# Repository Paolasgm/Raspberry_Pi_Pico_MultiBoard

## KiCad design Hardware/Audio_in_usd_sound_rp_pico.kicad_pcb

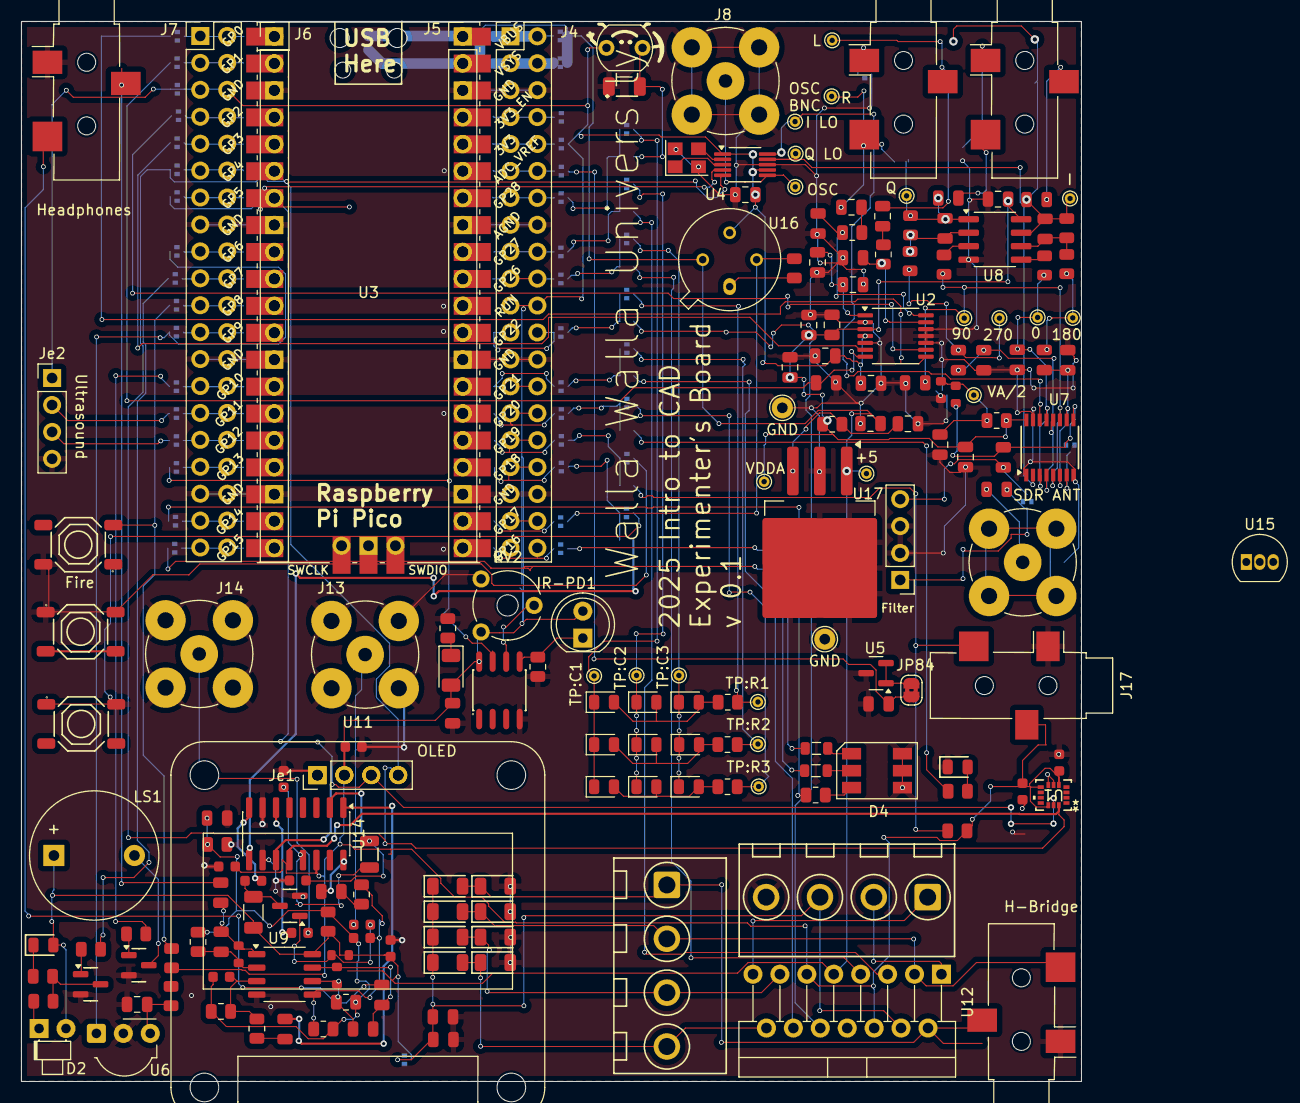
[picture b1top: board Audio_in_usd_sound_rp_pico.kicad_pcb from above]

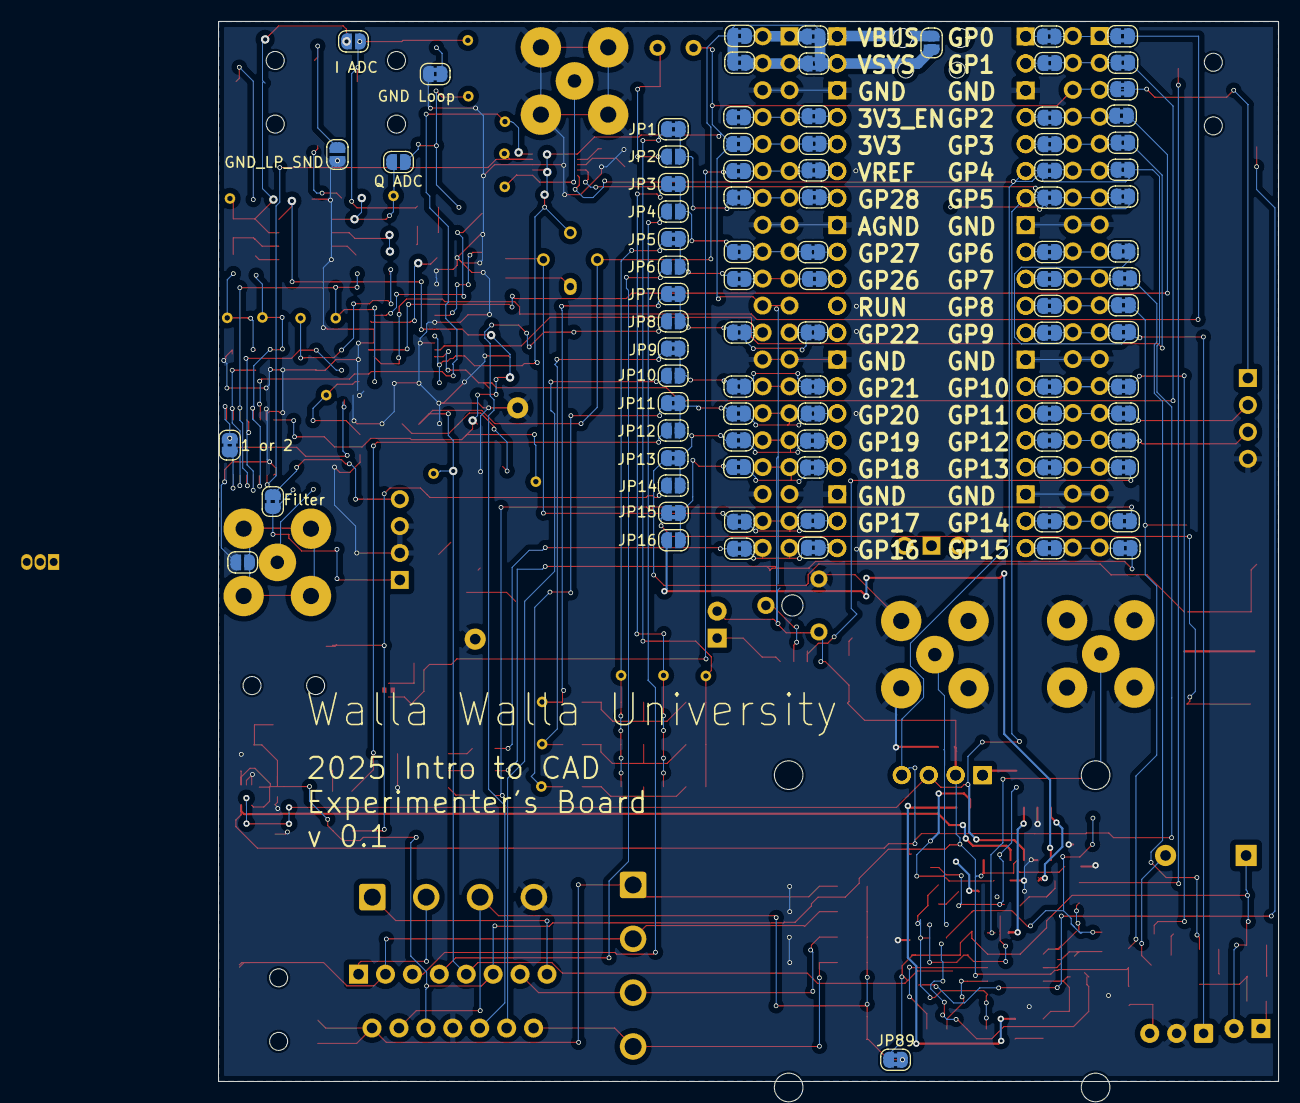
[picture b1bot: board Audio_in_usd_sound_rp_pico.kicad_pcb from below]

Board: 4 copper layers, 100.0 x 100.0 mm, 275 parts (88 on the bottom side), 189 nets.

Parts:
C2, C38, C41, C47, C48, C52: 100nF; C_0603
C3, C4: 1uF; C_0805_2012Metric
C6, C7, C16, C21, C22, C24, C27: 4.7nF; C_0805
C8, C9, C12, C56, C57: 10uF; C_0805_2012Metric
C10, C13, C17: 0.1uF; C_0805_2012Metric
C11, C15, C20, C23, C30, C55: 0.1u; C_0805_2012Metric
C14, C33, C42: 220pF; C_0805
C18, C19, C25, C26, C46: 1uF; C_0805
C28, C29: 100pF; C_0805
C31, C32, C39, C40, C44, C45: 10uF; C_0805
C34, C43: 10nF; C_0603
C35, C54: 2.2nF; C_0603
C36, C37: 22pF; C_0603
C49, C50, C51: 100nF; C_0805
D1, D3: Green; D_0805
D2: IR LED IR908-7C-F; LED_D1.8mm_W1.8mm_H2.4mm_Horizontal_O1.27mm_Z8.2mm
D4: C784540; LED footprint
D5, D6, D7, D8, D9, D10, D11, D12: 1N4004W; D_SOD-123FL
D13, D14, D15, D16, D17, D18, D19, D20, D21: LED; LED_0805_2012Metric
IR-LED1: IR26-21C_L110_TR8; LED_1206_3216Metric
IR-PD1: D_Photo; LED_D5.0mm
J1: ADC IN; Jack_3.5mm_CUI_SJ-3523-SMT_Horizontal
J4: Conn_02x20_Counter_Clockwise; PinSocket_2x20_P2.54mm_Vertical_Counterclockwise
J5, J6: Conn_01x20; PinHeader_1x20_P2.54mm_Vertical
J7: Conn_02x20_Counter_Clockwise; PinSocket_2x20_P2.54mm_Vertical
J8: BNC; BNC_TEConnectivity_1478204_Vertical
J11: SDR ANT; BNC_TEConnectivity_1478204_Vertical
J12: SDR Out; Jack_3.5mm_CUI_SJ-3523-SMT_Horizontal
J13, J14: ANT_BNC; BNC_TEConnectivity_1478204_Vertical
J15, J16: Audio IN; Jack_3.5mm_CUI_SJ-3523-SMT_Horizontal
J17: Mini-jack socket; Jack_3.5mm_CUI_SJ-3523-SMT_Horizontal
JP1, JP3, JP5, JP7, JP9, JP11, JP13, JP15, JP17, JP20, JP21, JP22, JP23, JP24, JP25, JP26, JP27, JP28, JP29, JP30, JP31, JP32, JP33, JP34, JP35, JP36, JP37, JP38, JP39, JP40, JP41, JP42, JP43, JP44, JP45, JP46, JP47, JP48, JP49, JP51, JP52, JP53, JP54, JP55, JP56, JP57, JP58, JP59, JP60, JP61, JP62, JP63, JP64, JP65, JP66, JP67, JP68, JP69, JP70, JP71, JP72, JP73, JP74, JP75, JP76, JP77, JP78, JP79, JP80, JP81, JP82, JP83, JP84, JP86, JP87, JP89: Jumper_2_Bridged; SolderJumper-2_P1.3mm_Bridged2Bar_RoundedPad1.0x1.5mm
JP2, JP4, JP6, JP8, JP10, JP12, JP14, JP16: Jumper_2_Open; SolderJumper-2_P1.3mm_Open_RoundedPad1.0x1.5mm
JP18, JP19, JP88: GND_LP_SND; SolderJumper-2_P1.3mm_Open_RoundedPad1.0x1.5mm
JP50: USB Only; SolderJumper-2_P1.3mm_Open_RoundedPad1.0x1.5mm
JP85: Groundloop RX_NS; SolderJumper-2_P1.3mm_Open_RoundedPad1.0x1.5mm
Je1, Je2: Conn_01x04_Socket; PinHeader_1x04_P2.54mm_Vertical_Female
Je3: Filter; PinHeader_1x04_P2.54mm_Vertical_Female
LS1: Speaker; Buzzer_12x9.5RM7.6
Q1, Q2: MMBT2222A 1P; Q_SOT-23
Q3: MMBT2222A; Q_SOT-23
R1: 10kΩ; R_0603
R2, R3: 200; R_0805_2012Metric
R4, R31, R43: 100Ω; R_0805
R5: 68Ω; R_0805
R6, R42: 10kΩ; R_0805
R7, R8: 1kΩ; R_0805
R9: 33Ω; R_0805
R10, R20: 39kΩ; R_0603
R11: 1kΩ; R_0603
R12: 10k; R_0805_2012Metric
R13, R14, R15, R16: 10Ω; R_0805
R17, R18, R29, R30: 2kΩ; R_0805
R19, R25: 15k; R_0805_2012Metric
R21, R27: 8.2k; R_0805_2012Metric
R22: 100kΩ; R_0603
R23, R28: 3.9k; R_0805_2012Metric
R24: 1k; R_1206_3216Metric
R32: B 100Ω; L_0805_2012Metric
R33: G 100Ω; L_0805_2012Metric
R34: R 300Ω; R_0805_2012Metric
R35: 10K; R_0805_2012Metric
R36: 270R; R_0805_2012Metric
R37: PhotoResistor; R_LDR_5.1x4.3mm_P3.4mm_Vertical
R38: 1kΩ; R_1206_3216Metric
R39, R40, R41: 680; R_0805_2012Metric
R44: 1; R_0805_2012Metric
RV2: R_Potentiometer_US; Potentiometer_Piher_PT-6-V_Vertical_Hole
S2: Tactile Button, 160gf; SW-SMD_4P-L5.1-W5.1-P3.70-LS6.5-TL-2
SW1: Left; SW-SMD_4P-L5.1-W5.1-P3.70-LS6.5-TL-2
SW2: Right; SW-SMD_4P-L5.1-W5.1-P3.70-LS6.5-TL-2
T1, T2: Screw Terminal, 4Px5.08mm, 20A; CONN-TH_4P-P5.08_DB129VG-5.08-4P-GN-S
TP1: L; TestPoint_THTPad_D1.0mm_Drill0.5mm
TP2: R; TestPoint_THTPad_D1.0mm_Drill0.5mm
TP3: I LO; TestPoint_THTPad_D1.0mm_Drill0.5mm
TP4: Q LO; TestPoint_THTPad_D1.0mm_Drill0.5mm
TP5: OSC; TestPoint_THTPad_D1.0mm_Drill0.5mm
TP10, TP12: GND; TestPoint_THTPad_D2.0mm_Drill1.0mm
TP11: VA/2; TestPoint_THTPad_D1.0mm_Drill0.5mm
TP13: 180; TestPoint_THTPad_D1.0mm_Drill0.5mm
TP14: 0; TestPoint_THTPad_D1.0mm_Drill0.5mm
TP15: 270; TestPoint_THTPad_D1.0mm_Drill0.5mm
TP16: 90; TestPoint_THTPad_D1.0mm_Drill0.5mm
TP17: I; TestPoint_THTPad_D1.0mm_Drill0.5mm
TP18: Q; TestPoint_THTPad_D1.0mm_Drill0.5mm
TP25: +5; TestPoint_THTPad_D1.0mm_Drill0.5mm
TP26: VDDA; TestPoint_THTPad_D1.0mm_Drill0.5mm
TP:C1, TP:C2, TP:C3: TestPoint; TestPoint_THTPad_D1.0mm_Drill0.5mm
TP:R1, TP:R2, TP:R3: TestPoint; TestPoint_THTPad_D1.0mm_Drill0.5mm
U1: LSM6DSO32TR; LGA-14L_2P5X3X0P83_STM
U2: PCM1808PWR; TSSOP-14_4.4x5mm_P0.65mm
U3: Pico; RPi_Pico_SMD_TH
U4: MS5351M; MSOP-10_3x3mm_P0.5mm
U5: CJ431; SOT-23
U6: TSOP4438; Vishay_MOLD-3Pin
U7: PI5C3253CQEX; SSOP-16_3.9x4.9mm_P0.635mm
U8: OPA1612AxD; SOIC-8_3.9x4.9mm_P1.27mm
U9: LM358; SOP-8_3.9x4.9mm_P1.27mm
U11: HS96L03W2C03; OLED
U12: L298N; TO-220-15_P2.54x2.54mm_StaggerOdd_Lead4.58mm_Vertical
U13: LM393DR2G; SOIC-8_L5.0-W4.0-P1.27-LS6.0-BL
U14: Si4732; SOIC-16_3.9x9.9mm_P1.27mm
U15: DS18B20A10T6; TO-92_Inline
U16: TO-33-4_Window-Taylan
U17: LM2937xS; TO-263-3_TabPin2
X1: Q13FC1350000400; FC-135R_L3.2-W1.5
Y1: X322525MSB4SI; Crystal_SMD_3225-4Pin_3.2x2.5mm

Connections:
+3.3V: C2.2, C8.1, C10.2, C15.2, C47.2, C48.1, C51.1, C52.2, IR-LED1.2 (A), IR-PD1.2 (A), J4.11, J4.30, J7.3, J7.38, J17.R, JP23.1 (A), JP69.1 (A), JP69.2 (B), Je1.2, Je2.1, R6.1, R9.2, R37.2, R42.1, RV2.1, U1.5 (VDDIO), U1.8 (VDD), U1.12 (CS), U2.4 (VDD), U4.1 (VDD), U4.7 (VDDO), U12.6 (EnA), U12.11 (EnB), U13.8 (VCC), U14.14 (VDD), U16.3 (VC)
+5V: C38.1, C55.1, D1.2, D2.2 (A), J5.2, JP20.1 (A), JP21.1 (A), JP35.2 (B), JP36.2 (B), JP50.2 (B), JP89.1 (A), LS1.1, R22.2, R24.1, R29.1, TP25.1, U3.39 (VSYS), U9.8 (V+), U12.9 (Vss), U16.1 (V0_1), U17.1 (VI)
/BCK: JP67.2 (B), U2.8 (BCK)
/BLUE: JP82.2 (B), R34.1
/Buzzer: JP78.2 (B), R8.2
/DATA: JP70.2 (B), U2.9 (DOUT)
/DRV1: JP4.1 (A), U12.5 (IN1)
/DRV2: JP6.1 (A), U12.7 (IN2)
/DRV3: JP8.1 (A), U12.10 (IN3)
/DRV4: JP10.1 (A), U12.12 (IN4)
/ECHO: JP80.2 (B), Je2.3
/Fire: JP76.2 (B), R6.2, S2.3 (C)
/GPIO18: JP15.2 (B), JP16.2 (B), JP32.1 (A)
/GPIO19: JP13.2 (B), JP14.2 (B), JP31.1 (A)
/GPIO20: JP11.2 (B), JP12.2 (B), JP30.1 (A)
/GPIO21: JP9.2 (B), JP10.2 (B), JP29.1 (A)
/GPIO22: JP7.2 (B), JP8.2 (B), JP28.1 (A)
/GPIO26: JP5.2 (B), JP6.2 (B), JP27.1 (A)
/GPIO27: JP3.2 (B), JP4.2 (B), JP26.1 (A)
/GPIO28: JP1.2 (B), JP2.2 (B), JP25.1 (A)
/GREEN: JP34.1 (A), R33.1
/I: C28.2, C31.1, JP18.2 (B), R17.2, TP17.1, U8.7
/IR_OUT: JP74.2 (B), JP77.2 (B), U6.1 (OUT)
/I_CLK: TP3.1, U4.10 (CLK0), U7.14 (S0)
/LED: JP12.1 (A), R31.1
/LeftButton: JP15.1 (A), SW1.1
/MatrixC1: JP7.1 (A), R39.1, TP:R1.1
/MatrixC2: JP9.1 (A), R40.1, TP:R2.1
/MatrixC3: JP11.1 (A), R41.1, TP:R3.1
/MatrixR1: D13.1 (K), D14.1 (K), D15.1 (K), JP1.1 (A), TP:C1.1
/MatrixR2: D16.1 (K), D17.1 (K), D18.1 (K), JP3.1 (A), TP:C2.1
/MatrixR3: D19.1 (K), D20.1 (K), D21.1 (K), JP5.1 (A), TP:C3.1
/PCM1808_ADC/VREF: C9.1, C11.2, U2.1 (VREF)
/PHOTO: JP2.1 (A), R37.1, R38.2
/PROX: JP81.2 (B), U13.7 (OUT/B)
/Q: C29.2, C32.1, JP19.1 (A), R18.2, TP18.1, U8.1
/Q_CLK: TP4.1, U4.9 (CLK1), U7.2 (S1)
/RED: JP83.2 (B), R32.1
/Raspberry_Pi_Pico/RST: J5.11, U3.30 (RUN)
/RightButton: JP13.1 (A), SW2.2
/SCKI: JP71.2 (B), U2.6 (SCKI)
/SCL: J6.7, JP56.1 (A), JP73.2 (B), Je1.3, U1.13 (SCL), U3.7 (GPIO5), U4.4 (SCL), U14.11 (SCLK)
/SDA: J6.6, JP55.1 (A), JP72.2 (B), Je1.4, U1.14 (SDA), U3.6 (GPIO4), U4.5 (SDA), U14.12 (SDIO)
/Shoot: JP75.2 (B), R7.2
/Si5351a/CLK2: J8.1 (In), TP5.1, U4.6 (CLK2)
/Smoke: JP33.1 (A), R43.1, U16.4 (V(RL))
/TRIG: JP79.2 (B), Je2.2
/Therm: J17.T, JP14.1 (A), R42.2
/VREF: C16.1, JP24.1 (A), JP84.2 (B)
/WS: C14.1, JP68.2 (B), U2.7 (LRCK)
/~RST: JP16.1 (A), U14.9 (~RST)
GND: C2.1, C6.2, C7.2, C8.2, C9.2, C10.1, C11.1, C12.2, C13.1, C14.2, C15.1, C16.2, C17.2, C20.1, C21.2, C22.2, C23.1, C24.2, C27.2, C30.1, C36.1, C37.2, C38.2, C46.2, C47.1, C48.2, C49.2, C50.2, C51.2, C52.1, C55.2, C56.2, C57.2, D3.1, D4.4 (BK), D4.5 (RK), D4.6 (GK), D6.2, D8.2, D10.2, D12.2, J4.3, J4.8, J4.13, J4.18, J4.23, J4.28, J4.33, J4.38, J5.3, J5.8, J5.13, J5.18, J6.3, J6.8, J6.13, J6.18, J7.8, J7.13, J7.18, J7.23, J7.28, J7.33, J8.2 (Ext), J13.2 (Ext), J14.2 (Ext), J15.S, J16.S, J17.S, JP17.1 (A), JP85.1 (A), JP88.1 (A), Je1.1, Je2.4, Je3.2, Je3.3, Q1.2 (E), Q2.2 (E), Q3.2 (E), R1.1, R30.2, R35.2, R36.2, R38.1, RV2.3, S2.2 (B), SW1.2, SW2.1, T1.4, TP10.1, TP12.1, U1.6 (GND), U1.7 (GND), U2.2 (AGND), U2.5 (DGND), U2.10 (MD0), U2.11 (MD1), U2.12 (FMT), U3.3 (GND), U3.8 (GND), U3.13 (GND), U3.18 (GND), U3.23 (GND), U3.28 (GND), U3.33 (AGND), U3.38 (GND), U4.8 (GND), U5.3 (A), U6.2 (GND), U7.1 (1~OE), U7.8 (GND), U7.15 (2~OE), U8.4 (V-), U9.4 (V-), U12.8 (GND), U13.4 (GND), U14.7 (RFGND), U14.10 (~SEN), U14.15 (GND), U17.2 (GND), Y1.2, Y1.4
GND1: C35.2, C46.1, C54.2, R19.2, R21.2, R25.2, R27.2, R29.2, R30.1
unnamed: C3.2, R2.1
unnamed: C4.2, R3.1
unnamed: C20.2, R1.2, R11.1, R12.2, TP11.1
unnamed: C25.2, R13.1, TP13.1
unnamed: C26.2, R16.1, TP15.1
unnamed: C31.2, J12.R
unnamed: C32.2, J12.T
unnamed: C33.1, C39.2, R10.1, U9.1
unnamed: C39.1, J15.R
unnamed: C40.1, R23.2
unnamed: C42.1, C44.2, R20.1, U9.7
unnamed: C44.1, J15.T
unnamed: C45.1, R28.1
unnamed: D1.1, R4.1
unnamed: D2.1 (K), R5.1
unnamed: D3.2, R31.2
unnamed: D4.3 (BA), R34.2
unnamed: D4.1 (GA), R33.2
unnamed: D4.2 (RA), R32.2
unnamed: D13.2 (A), D16.2 (A), D19.2 (A), R39.2
unnamed: D14.2 (A), D17.2 (A), D20.2 (A), R40.2
unnamed: D15.2 (A), D18.2 (A), D21.2 (A), R41.2
unnamed: IR-LED1.1 (K), R36.1
unnamed: IR-PD1.1 (K), R35.1, U13.5 (IN/B)
unnamed: J4.1, J4.40, JP20.2 (B), JP35.1 (A)
unnamed: J4.2, J4.39, JP21.2 (B), JP36.1 (A)
unnamed: J4.10, J4.31, JP27.2 (B), JP42.1 (A)
unnamed: J4.12, J4.29, JP28.2 (B), JP43.1 (A)
unnamed: J4.14, J4.27, JP29.2 (B), JP44.1 (A)
unnamed: J4.15, J4.26, JP30.2 (B), JP45.1 (A)
unnamed: J4.16, J4.25, JP31.2 (B), JP46.1 (A)
unnamed: J4.17, J4.24, JP32.2 (B), JP47.1 (A)
unnamed: J4.19, J4.22, JP33.2 (B), JP48.1 (A)
unnamed: J4.20, J4.21, JP34.2 (B), JP49.1 (A)
unnamed: J4.9, J4.32, JP26.2 (B), JP41.1 (A)
unnamed: J4.7, J4.34, JP25.2 (B), JP40.1 (A)
unnamed: J4.6, J4.35, JP24.2 (B), JP39.1 (A)
unnamed: J4.5, J4.36, JP23.2 (B), JP38.1 (A)
unnamed: J4.4, J4.37, JP22.2 (B), JP37.1 (A)
unnamed: J5.1, JP50.1 (A), U3.40 (VBUS)
unnamed: J5.4, JP37.2 (B), U3.37 (3V3_EN)
unnamed: J5.5, JP38.2 (B), U3.36 (3V3)
unnamed: J5.6, JP39.2 (B), U3.35 (ADC_VREF)
unnamed: J5.7, JP40.2 (B), U3.34 (GPIO28_ADC2)
unnamed: J5.9, JP41.2 (B), U3.32 (GPIO27_ADC1)
unnamed: J5.10, JP42.2 (B), U3.31 (GPIO26_ADC0)
unnamed: J5.12, JP43.2 (B), U3.29 (GPIO22)
unnamed: J5.14, JP44.2 (B), U3.27 (GPIO21)
unnamed: J5.15, JP45.2 (B), U3.26 (GPIO20)
unnamed: J5.16, JP46.2 (B), U3.25 (GPIO19)
unnamed: J5.17, JP47.2 (B), U3.24 (GPIO18)
unnamed: J5.19, JP48.2 (B), U3.22 (GPIO17)
unnamed: J5.20, JP49.2 (B), U3.21 (GPIO16)
unnamed: J6.1, JP51.1 (A), U3.1 (GPIO0)
unnamed: J6.2, JP52.1 (A), U3.2 (GPIO1)
unnamed: J6.4, JP53.1 (A), U3.4 (GPIO2)
unnamed: J6.5, JP54.1 (A), U3.5 (GPIO3)
unnamed: J6.9, JP57.1 (A), U3.9 (GPIO6)
unnamed: J6.10, JP58.1 (A), U3.10 (GPIO7)
unnamed: J6.11, JP59.1 (A), U3.11 (GPIO8)
unnamed: J6.12, JP60.1 (A), U3.12 (GPIO9)
unnamed: J6.14, JP61.1 (A), U3.14 (GPIO10)
unnamed: J6.15, JP62.1 (A), U3.15 (GPIO11)
unnamed: J6.16, JP63.1 (A), U3.16 (GPIO12)
unnamed: J6.17, JP64.1 (A), U3.17 (GPIO13)
unnamed: J6.19, JP65.1 (A), U3.19 (GPIO14)
unnamed: J6.20, JP66.1 (A), U3.20 (GPIO15)
unnamed: J7.1, J7.40, JP51.2 (B), JP67.1 (A)
unnamed: J7.2, J7.39, JP52.2 (B), JP68.1 (A)
unnamed: J7.10, J7.31, JP58.2 (B), JP75.1 (A)
unnamed: J7.11, J7.30, JP59.2 (B), JP76.1 (A)
unnamed: J7.12, J7.29, JP60.2 (B), JP77.1 (A)
unnamed: J7.14, J7.27, JP61.2 (B), JP78.1 (A)
unnamed: J7.15, J7.26, JP62.2 (B), JP79.1 (A)
unnamed: J7.16, J7.25, JP63.2 (B), JP80.1 (A)
unnamed: J7.17, J7.24, JP64.2 (B), JP81.1 (A)
unnamed: J7.19, J7.22, JP65.2 (B), JP82.1 (A)
unnamed: J7.20, J7.21, JP66.2 (B), JP83.1 (A)
unnamed: J7.9, J7.32, JP57.2 (B), JP74.1 (A)
unnamed: J7.7, J7.34, JP56.2 (B), JP73.1 (A)
unnamed: J7.6, J7.35, JP55.2 (B), JP72.1 (A)
unnamed: J7.5, J7.36, JP54.2 (B), JP71.1 (A)
unnamed: J7.4, J7.37, JP53.2 (B), JP70.1 (A)
unnamed: J11.2 (Ext), JP85.2 (B)
unnamed: C18.1, J11.1 (In)
unnamed: C43.1, J13.1 (In)
unnamed: C34.1, J14.1 (In)
unnamed: J1.S, JP17.2 (B)
unnamed: C3.1, J1.R, JP18.1 (A), TP1.1
unnamed: C4.1, J1.T, JP19.2 (B), TP2.1
unnamed: JP84.1 (A), U5.1 (REF), U5.2 (K)
unnamed: C18.2, JP86.1 (A), Je3.1
unnamed: C19.1, JP86.2 (B), Je3.4
unnamed: JP87.1 (A), U7.7 (1A)
unnamed: C19.2, JP87.2 (B), R11.2, U7.9 (2A)
unnamed: J12.S, JP88.2 (B)
unnamed: Q1.1 (B), R7.1
unnamed: Q1.3 (C), R4.2, R5.2
unnamed: Q2.1 (B), R8.1
unnamed: LS1.2, Q2.3 (C)
unnamed: C43.2, Q3.1 (B), R22.1
unnamed: C41.2, Q3.3 (C), R24.2
unnamed: C6.1, R2.2, U2.13 (VINL)
unnamed: C7.1, R3.2, U2.14 (VINR)
unnamed: U4.2 (XA), Y1.3
unnamed: U4.3 (XB), Y1.1
unnamed: C17.1, R9.1, U6.3 (Vs)
unnamed: C25.1, C27.1, U7.6 (1B1), U7.10 (2B1)
unnamed: C24.1, R15.1, TP16.1, U7.5 (1B2), U7.11 (2B2)
unnamed: C22.1, C26.1, U7.4 (1B3), U7.12 (2B3)
unnamed: C21.1, R14.1, TP14.1, U7.3 (1B4), U7.13 (2B4)
unnamed: R15.2, U8.3 (+)
unnamed: C29.1, R16.2, R18.1, U8.2 (-)
unnamed: R14.2, U8.5 (+)
unnamed: C28.1, R13.2, R17.1, U8.6 (-)
unnamed: C35.1, R21.1, R23.1, U9.3 (+)
unnamed: C33.2, R10.2, R19.1, U9.2 (-)
unnamed: C54.1, R27.1, R28.2, U9.5 (+)
unnamed: C42.2, R20.2, R25.1, U9.6 (-)
unnamed: D7.2, D8.1, J16.R, T2.1, U12.2 (OUT1)
unnamed: D11.2, D12.1, J16.T, T2.2, U12.3 (OUT2)
unnamed: D5.2, D6.1, T2.3, U12.13 (OUT3)
unnamed: D9.2, D10.1, T2.4, U12.14 (OUT4)
unnamed: T1.2, U12.1 (SENSE_A)
unnamed: T1.1, U12.15 (SENSE_B)
unnamed: RV2.2, U13.6 (IN/B/2)
unnamed: C41.1, U14.8 (AMI)
unnamed: C37.1, U14.2 (DCLK), X1.1
unnamed: C34.2, U14.6 (FMI)
unnamed: C40.2, U14.1 (LOUT)
unnamed: C36.2, U14.13 (RCLK), X1.2
unnamed: C45.2, U14.16 (ROUT)
unnamed: C56.1, R44.2, U17.3 (VO)
VDDA: C12.1, C13.2, C23.2, C30.2, C57.1, R12.1, R44.1, TP26.1, U2.3 (VCC), U7.16 (VCC), U8.8 (V+)
VS: C49.1, C50.1, D5.1, D7.1, D9.1, D11.1, JP89.2 (B), T1.3, U12.4 (Vs)
~: R43.2, U16.2 (V0_2)

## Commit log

2026-03-11 Fix Si4732
2026-03-11 Fixes (I fixed the Si4732)
    Isolate the YD's remapped signals so the project keeps control of power and ADC: open the YD pin‑37 solder jumper and JP2 (disconnect GPIO23/RGB), close JP1 to tie ADC_VREF to +3V3 (use external VREF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
2026-03-11 Actual pcb and sch changes
    I switched the pin numbers that were backwards
